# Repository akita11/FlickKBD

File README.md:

# FlickKBD

静電容量式タッチ検出を使った名刺サイズのフリック入力キーボードです。PC等にUSB(Type-C)で接続し、キーボードとして使うことができます。
かな（ローマ字入力）、英字、数字の3つのモードがあります。

※感度・入力速度はサポートページ内の動画からご確認ください。スマホのフリック入力ほどの実用性はありませんのでご了承ください。またPC等側のキーボードの設定（英字キーボード等）によっては、表示されているものと異なる文字が入力されることがあります。またタッチ検出の補正動作によって、非タッチ時にタッチが検出されてLEDが消灯している場合は、少し待つとLEDが点灯して入力できるようになります。

[動作原理と使用例（動画）(ProtoPedia)](https://protopedia.net/prototype/9148)

## 使い方

本機のUSB Type-Cコネクタ（基板と一体化）にUSB Type-Cケーブルを刺し、PC等に接続します。
PC等からはUSBキーボードとして認識されます。
（本機には2つのUSBコネクタがありますが、どちらでもOKです）

### 文字入力

やや強めにタッチしつつゆっくり移動させてフリック入力ができます。
（カッコ内は、左上のキーの場合の入力される文字例）

- タッチのみ: 基本文字（"a"）
- タッチ後、左にマス目の半分ほど移動：左フリック（"i"）
- タッチ後、上にマス目の半分ほど移動：上フリック（"u"）
- タッチ後、右にマス目の半分ほど移動：上フリック（"e"）
- タッチ後、下にマス目の半分ほど移動：上フリック（"o"）

LED表示は以下の意味で、タッチやフリック動作の検出状況を確認できます。
- 非タッチ時に点灯
- タッチ時に消灯
- 左or右フリック検出時に1回点滅
- 上or下フリック検出時に2回点滅、

なお、かな（ローマ字）入力モード時に"A/a"キー（左下）を押してから（LEDがやや暗くなる）文字入力を行うと小文字が入力されます。（例："あ(a)"→"ぁ(xa)"

また、アルファベット入力モード時に"A/a"キー（左下）を押すと、大文字／小文字モードが切り替わります（小文字入力時はLEDがやや暗くなります）

### 入力モード

"あA1"キー（右端上から2つめ）を押すと、入力モードが切り替わり、以下のようにLEDの色が変わります。

- かな（ローマ字）入力モード: 緑
- アルファベット入力モード: 青
- 数字・記号入力モード: 赤

## プログラムの書き換え

ArduinoIDEに、[CH55xduino](https://github.com/DeqingSun/ch55xduino)をインストールし、2つのUSBコネクタからそれぞれのマイコン(CH552)に書き込みます。
事前に、TouchKey.{c,h}を、ArduinoIDEフォルダ内のCH55xduinoフォルダのTouchKey/srcにコピーしてださい（念のため、オリジナルのCH55xduinoの両ファイルはバックアップをとっておいてください）。
（Macの場合は、~/Library/Arduino15/packages/CH55xDuino/hardware/mcs51/0.0.26/libraries/TouchKey/src）
- USB Settingを"USER CODE w/128B USB RAM"に変更
- 上側のUSBコネクタ: FlickKBD.ino中の"#define DEV_R"をコメントアウトし、書き込み
- 右側のUSBコネクタ: FlickKBD.ino中の"#define DEV_R"を残して、書き込み

なおブランクのCH552に初回書き込み時以外は、CH552を、以下の手順でダウンロードモードに設定してください。
- 右側のUSBコネクタ使用時: 裏面の上図の"1-2"間をジャンパ線等でショートした状態で右側USBコネクタに接続し、1秒ほど保持してからショートを解除する
- 上側のUSBコネクタ使用時: 裏面の上図の"2-3"間をジャンパ線等でショートした状態で右側USBコネクタに接続し、1秒ほど保持してからショートを解除する

## Author

Junichi Akita (akita@ifdl.jp / @akita11)

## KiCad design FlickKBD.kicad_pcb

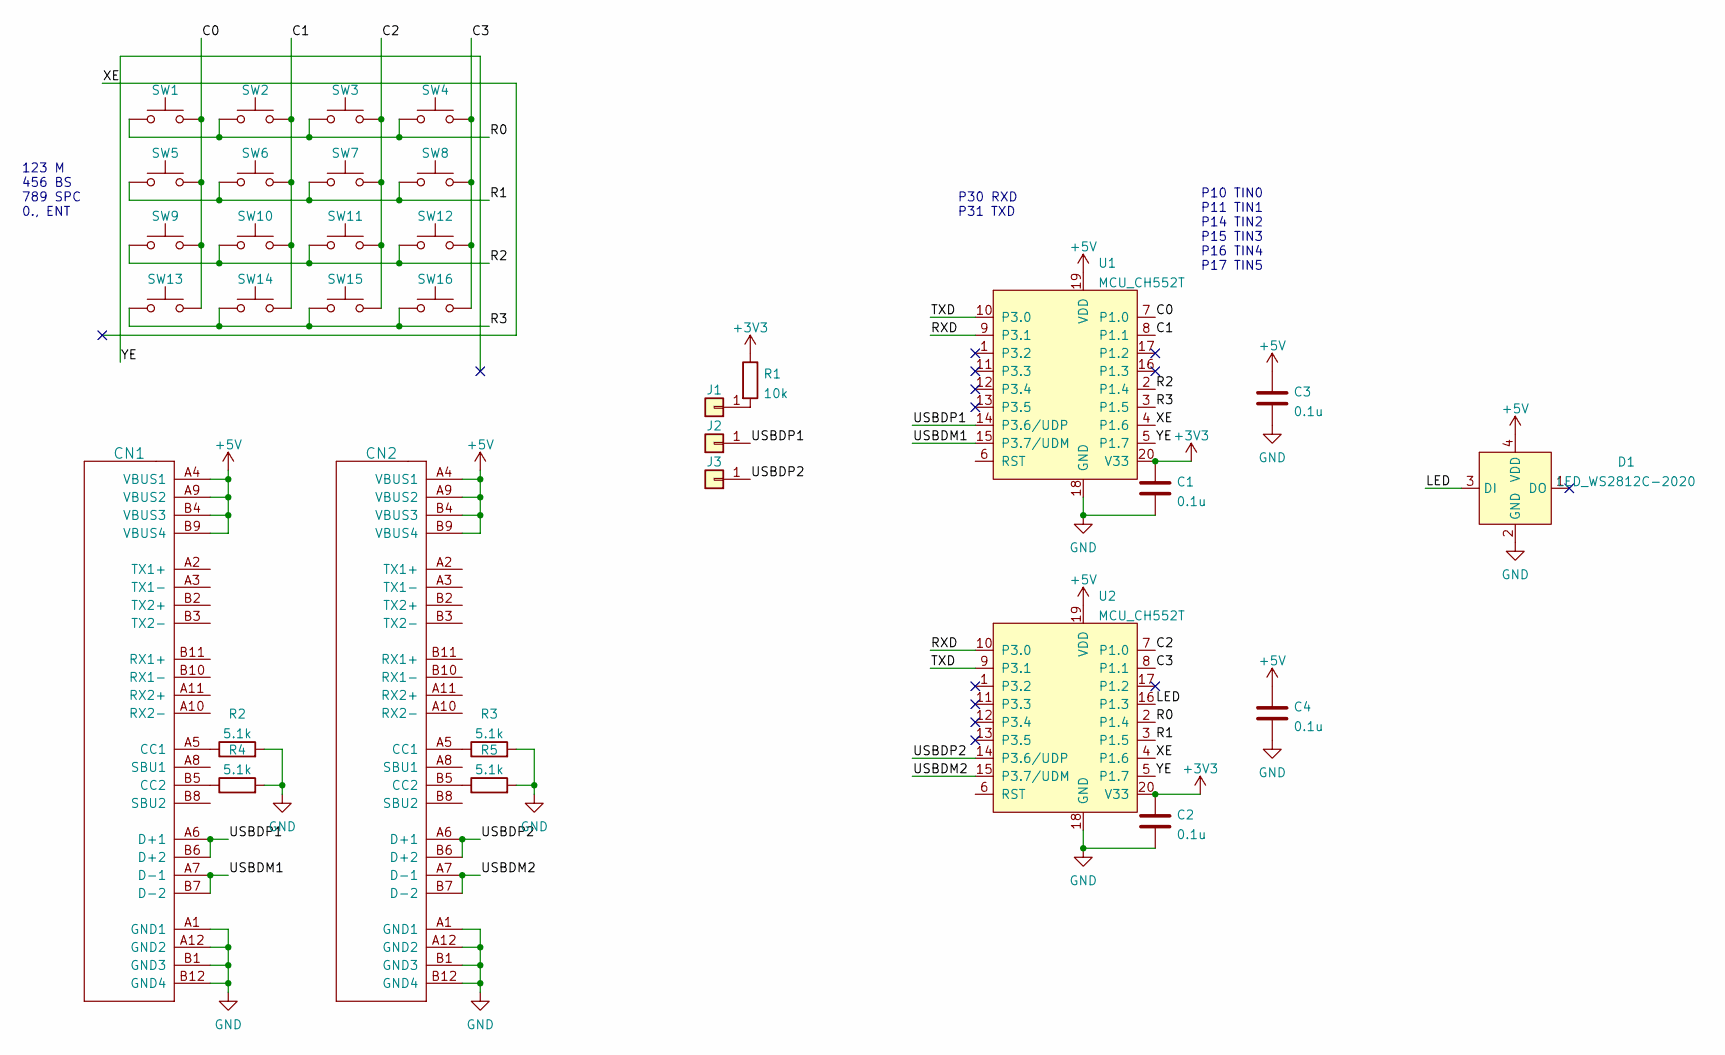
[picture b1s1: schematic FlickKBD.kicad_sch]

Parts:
C1, C2, C3, C4: 0.1u; C_0603_1608Metric
CN1, CN2: CON_USB-CPCBPLUG; USB-C_PCBPLUG
D1: LED_WS2812C-2020; LED_2020_4p
J1, J2, J3: Conn_01x01; Pad_SMD1.6mm
R1: 10k; R_0603_1608Metric
R2, R3, R4, R5: 5.1k; R_0603_1608Metric
SW1, SW2, SW3, SW4, SW5, SW6, SW7, SW8, SW9, SW10, SW11, SW12, SW13, SW14, SW15, SW16: SW_Push; SMD_Key_11mmX_p13mm
U1, U2: MCU_CH552T; TSSOP-20_4.4x6.5mm_P0.65mm

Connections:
+3V3: C1.1, C2.1, R1.1, U1.20 (V33), U2.20 (V33)
+5V: C3.1, C4.1, CN1.A4 (VBUS1), CN1.A9 (VBUS2), CN1.B4 (VBUS3), CN1.B9 (VBUS4), CN2.A4 (VBUS1), CN2.A9 (VBUS2), CN2.B4 (VBUS3), CN2.B9 (VBUS4), D1.4 (VDD), U1.19 (VDD), U2.19 (VDD)
/C0: SW1.1, SW5.1, SW9.1, SW13.1, U1.7 (P1.0)
/C1: SW2.1, SW6.1, SW10.1, SW14.1, U1.8 (P1.1)
/C2: SW3.1, SW7.1, SW11.1, SW15.1, U2.7 (P1.0)
/C3: SW4.1, SW8.1, SW12.1, SW16.1, U2.8 (P1.1)
/LED: D1.3 (DI), U2.16 (P1.3)
/R0: SW1.2, SW2.2, SW3.2, SW4.2, U2.2 (P1.4)
/R1: SW5.2, SW6.2, SW7.2, SW8.2, U2.3 (P1.5)
/R2: SW9.2, SW10.2, SW11.2, SW12.2, U1.2 (P1.4)
/R3: SW13.2, SW14.2, SW15.2, SW16.2, U1.3 (P1.5)
/RXD: U1.9 (P3.1), U2.10 (P3.0)
/TXD: U1.10 (P3.0), U2.9 (P3.1)
/USBDM1: CN1.A7 (D-1), CN1.B7 (D-2), U1.15 (P3.7/UDM)
/USBDM2: CN2.A7 (D-1), CN2.B7 (D-2), U2.15 (P3.7/UDM)
/USBDP1: CN1.A6 (D+1), CN1.B6 (D+2), J2.1, U1.14 (P3.6/UDP)
/USBDP2: CN2.A6 (D+1), CN2.B6 (D+2), J3.1, U2.14 (P3.6/UDP)
/XE: U1.4 (P1.6), U2.4 (P1.6); also elsewhere on the board
/YE: U1.5 (P1.7), U2.5 (P1.7); also elsewhere on the board
GND: C1.2, C2.2, C3.2, C4.2, CN1.A1 (GND1), CN1.A12 (GND2), CN1.B1 (GND3), CN1.B12 (GND4), CN2.A1 (GND1), CN2.A12 (GND2), CN2.B1 (GND3), CN2.B12 (GND4), D1.2 (GND), R2.2, R3.2, R4.2, R5.2, U1.18 (GND), U2.18 (GND)
unnamed: CN1.A5 (CC1), R2.1
unnamed: CN1.B5 (CC2), R4.1
unnamed: CN2.A5 (CC1), R3.1
unnamed: CN2.B5 (CC2), R5.1
unnamed: J1.1, R1.2

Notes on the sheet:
P10 TIN0 P11 TIN1 P14 TIN2 P15 TIN3 P16 TIN4 P17 TIN5
123 M 456 BS 789 SPC 0., ENT
P30 RXD P31 TXD

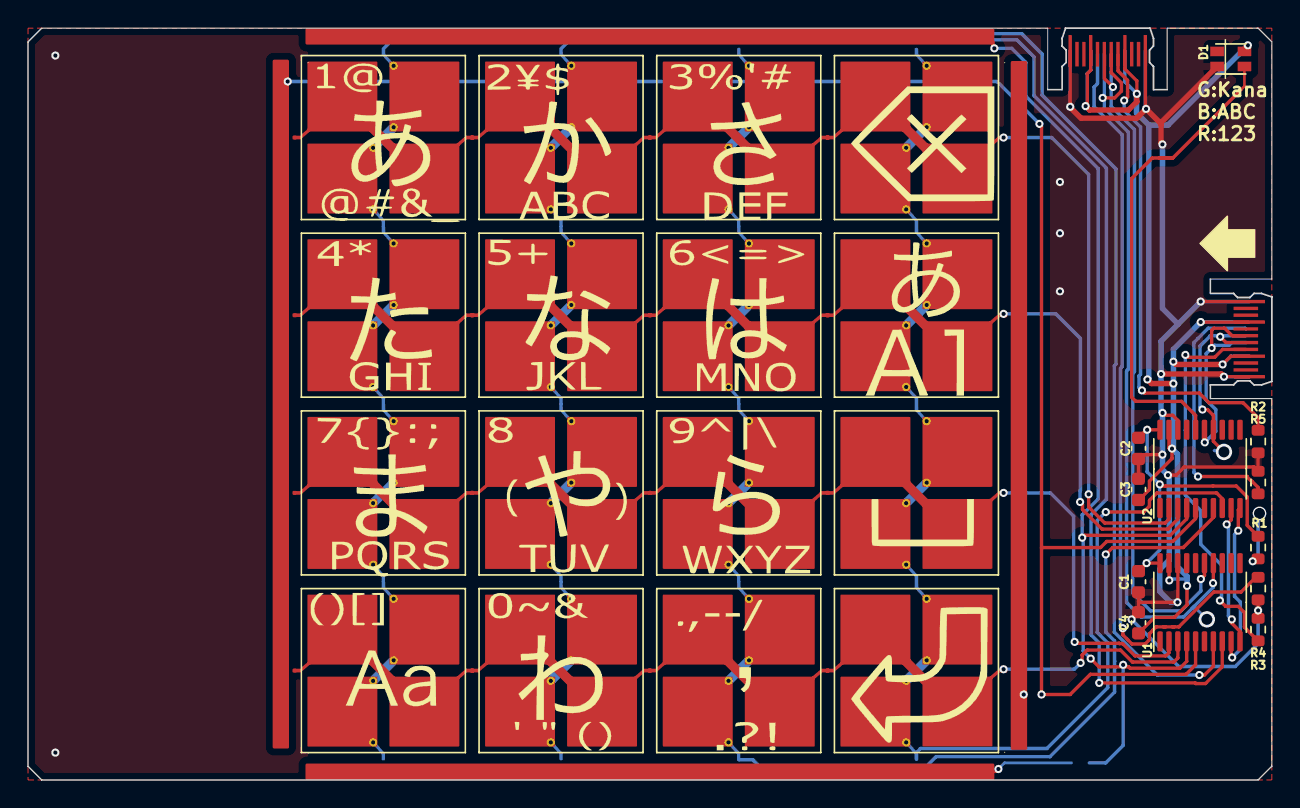
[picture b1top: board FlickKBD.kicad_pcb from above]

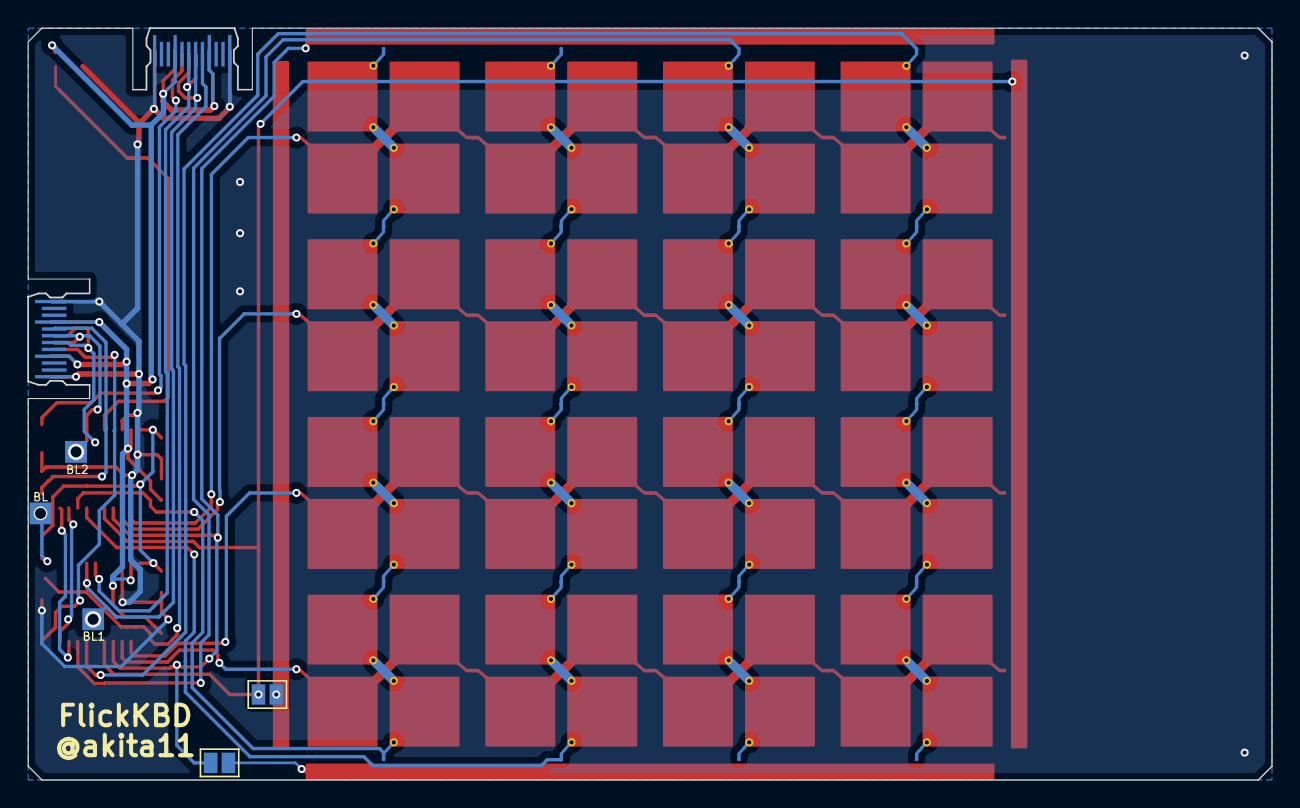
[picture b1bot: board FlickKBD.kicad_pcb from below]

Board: 2 copper layers, 91.0 x 55.0 mm, 35 parts (5 on the bottom side), 25 nets.

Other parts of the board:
JP1, JP2: Jumper_2_Open; SolderJumper-2_P1.3mm_Open_Pad1.0x1.5mm

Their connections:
/XE: JP1.1 (A); also elsewhere on the board
/YE: JP2.1 (A); also elsewhere on the board
